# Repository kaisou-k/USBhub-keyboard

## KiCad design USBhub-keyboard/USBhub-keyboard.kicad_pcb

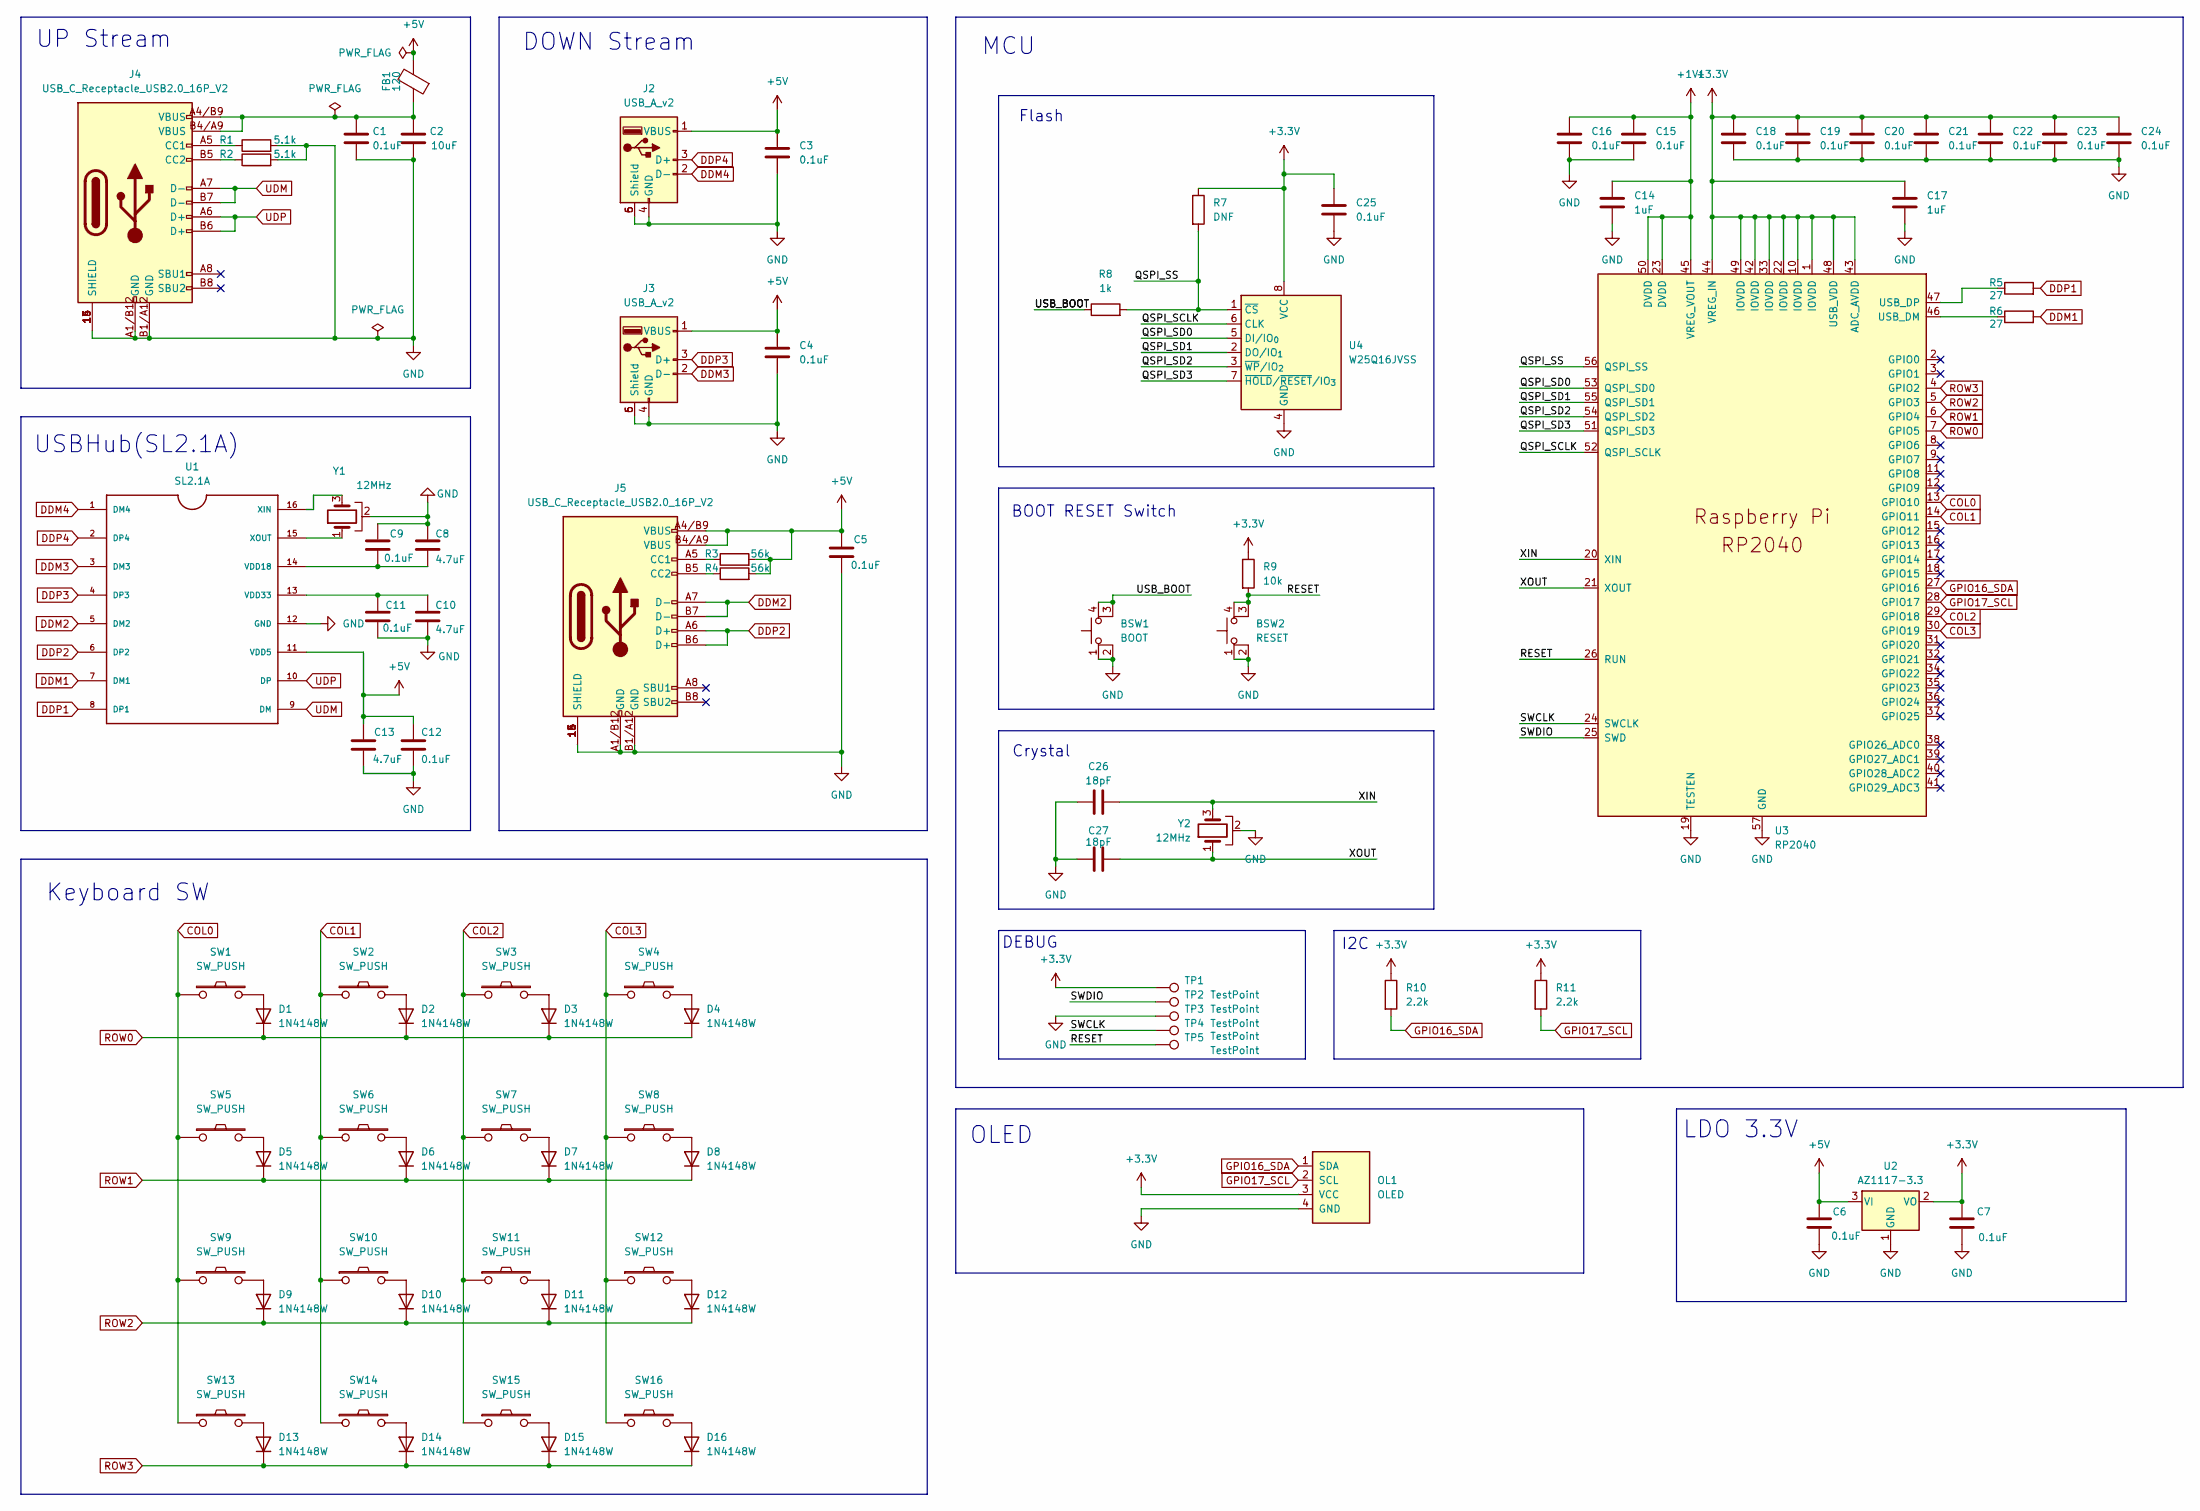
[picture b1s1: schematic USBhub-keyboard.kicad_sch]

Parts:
BSW1: BOOT; SW_TS04-66-50-BK-260-SMT
BSW2: RESET; SW_TS04-66-50-BK-260-SMT
C1, C3, C4, C5, C6, C7, C9, C11, C12, C15, C16, C18, C19, C20, C21, C22, C23, C24, C25: 0.1uF; C_0603_1608Metric
C2: 10uF; C_0805_2012Metric
C8, C10, C13: 4.7uF; C_1206_3216Metric
C14, C17: 1uF; C_0805_2012Metric
C26, C27: 18pF; C_0603_1608Metric
D1, D2, D3, D4, D5, D6, D7, D8, D9, D10, D11, D12, D13, D14, D15, D16: 1N4148W; D_SOD-123
FB1: 120; R_0603_1608Metric
J2, J3: USB_A_v2; 3210W1BCE
J4, J5: USB_C_Receptacle_USB2.0_16P_V2; CONN_8p94X6p5X3p16_12L_GCC
OL1: OLED; 128x64OLED
R1, R2: 5.1k; R_0603_1608Metric
R3, R4: 56k; R_0603_1608Metric
R5, R6: 27; R_0603_1608Metric
R7: DNF; R_0603_1608Metric
R8: 1k; R_0603_1608Metric
R9: 10k; R_0603_1608Metric
R10, R11: 2.2k; R_0603_1608Metric
SW1, SW2, SW3, SW4, SW5, SW6, SW7, SW8, SW9, SW10, SW11, SW12, SW13, SW14, SW15, SW16: SW_PUSH; CherryMX_Hotswap_via_1U
TP1, TP2, TP3, TP4, TP5: TestPoint; TestPoint_Pad_1.5x1.5mm
U1: SL2.1A; SO16
U2: AZ1117-3.3; SOT-223-3_TabPin2
U3: RP2040; RP2040-QFN-56
U4: W25Q16JVSS; SOIC-8_5.3x5.3mm_P1.27mm
Y1, Y2: 12MHz; Crystal_SMD_3225-4Pin_3.2x2.5mm

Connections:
+1V1: C14.1, C15.1, C16.1, U3.23 (DVDD), U3.45 (VREG_VOUT), U3.50 (DVDD)
+3.3V: C7.1, C17.1, C18.1, C19.1, C20.1, C21.1, C22.1, C23.1, C24.1, C25.1, OL1.3 (VCC), R7.1, R9.1, R10.1, R11.1, TP1.1, U2.2 (VO), U3.1 (IOVDD), U3.10 (IOVDD), U3.22 (IOVDD), U3.33 (IOVDD), U3.42 (IOVDD), U3.43 (ADC_AVDD), U3.44 (VREG_IN), U3.48 (USB_VDD), U3.49 (IOVDD), U4.8 (VCC); also elsewhere on the board
+5V: C3.1, C4.1, C5.1, C6.1, C12.1, C13.1, FB1.2, J2.1 (VBUS), J3.1 (VBUS), J5.A4/B9 (VBUS), J5.A9 (VBUS), J5.B4 (VBUS), J5.B4/A9 (VBUS), J5.B9 (VBUS), R3.2, R4.2, U1.11 (VDD5), U2.3 (VI)
/QSPI_SCLK: U3.52 (QSPI_SCLK), U4.6 (CLK)
/QSPI_SD0: U3.53 (QSPI_SD0), U4.5 (DI/IO_{0})
/QSPI_SD1: U3.55 (QSPI_SD1), U4.2 (DO/IO_{1})
/QSPI_SD2: U3.54 (QSPI_SD2), U4.3 (~WP/IO_{2})
/QSPI_SD3: U3.51 (QSPI_SD3), U4.7 (~HOLD/~RESET/IO_{3})
/QSPI_SS: R7.2, R8.2, U3.56 (QSPI_SS), U4.1 (~CS)
/RESET: BSW2.3 (K), BSW2.4 (A), R9.2, TP5.1, U3.26 (RUN); also elsewhere on the board
/SWCLK: TP4.1, U3.24 (SWCLK); also elsewhere on the board
/SWDIO: TP2.1, U3.25 (SWD); also elsewhere on the board
/USB_BOOT: BSW1.3 (K), BSW1.4 (A), R8.1
/XIN: C26.2, U3.20 (XIN), Y2.3
/XOUT: C27.2, U3.21 (XOUT), Y2.1
COL0: SW1.1, SW5.1, SW9.1, SW13.1, U3.13 (GPIO10)
COL1: SW2.1, SW6.1, SW10.1, SW14.1, U3.14 (GPIO11)
COL2: SW3.1, SW7.1, SW11.1, SW15.1, U3.29 (GPIO18)
COL3: SW4.1, SW8.1, SW12.1, SW16.1, U3.30 (GPIO19)
DDM1: R6.2, U1.7 (DM1)
DDM2: J5.A7 (D-), J5.B7 (D-), U1.5 (DM2)
DDM3: J3.2 (D-), U1.3 (DM3)
DDM4: J2.2 (D-), U1.1 (DM4)
DDP1: R5.2, U1.8 (DP1)
DDP2: J5.A6 (D+), J5.B6 (D+), U1.6 (DP2)
DDP3: J3.3 (D+), U1.4 (DP3)
DDP4: J2.3 (D+), U1.2 (DP4)
GND: BSW1.1, BSW1.2, BSW2.1, BSW2.2, C1.2, C2.2, C3.2, C4.2, C5.2, C6.2, C7.2, C8.1, C9.1, C10.2, C11.2, C12.2, C13.2, C14.2, C15.2, C16.2, C17.2, C18.2, C19.2, C20.2, C21.2, C22.2, C23.2, C24.2, C25.2, C26.1, C27.1, J2.4 (GND), J2.5 (Shield), J2.6 (Shield), J3.4 (GND), J3.5 (Shield), J3.6 (Shield), J4.13 (SHIELD), J4.14 (SHIELD), J4.15 (SHIELD), J4.16 (SHIELD), J4.A1/B12 (GND), J4.A12 (GND), J4.B1 (GND), J4.B1/A12 (GND), J4.B12 (GND), J5.13 (SHIELD), J5.14 (SHIELD), J5.15 (SHIELD), J5.16 (SHIELD), J5.A1/B12 (GND), J5.A12 (GND), J5.B1 (GND), J5.B1/A12 (GND), J5.B12 (GND), OL1.4 (GND), R1.2, R2.2, TP3.1, U1.12 (GND), U2.1 (GND), U3.19 (TESTEN), U3.57 (GND), U4.4 (GND), Y1.2, Y1.4, Y2.2, Y2.4; also elsewhere on the board
GPIO16_SDA: OL1.1 (SDA), R10.2, U3.27 (GPIO16)
GPIO17_SCL: OL1.2 (SCL), R11.2, U3.28 (GPIO17)
unnamed: C1.1, C2.1, FB1.1, J4.A4/B9 (VBUS), J4.A9 (VBUS), J4.B4 (VBUS), J4.B4/A9 (VBUS), J4.B9 (VBUS)
unnamed: D1.2 (A), SW1.2
unnamed: D2.2 (A), SW2.2
unnamed: D3.2 (A), SW3.2
unnamed: D4.2 (A), SW4.2
unnamed: D5.2 (A), SW5.2
unnamed: D6.2 (A), SW6.2
unnamed: D7.2 (A), SW7.2
unnamed: D8.2 (A), SW8.2
unnamed: D9.2 (A), SW9.2
unnamed: D10.2 (A), SW10.2
unnamed: D11.2 (A), SW11.2
unnamed: D12.2 (A), SW12.2
unnamed: D13.2 (A), SW13.2
unnamed: D14.2 (A), SW14.2
unnamed: D15.2 (A), SW15.2
unnamed: D16.2 (A), SW16.2
unnamed: J4.A5 (CC1), R1.1
unnamed: J4.B5 (CC2), R2.1
unnamed: J5.A5 (CC1), R3.1
unnamed: J5.B5 (CC2), R4.1
unnamed: C8.2, C9.2, U1.14 (VDD18)
unnamed: C10.1, C11.1, U1.13 (VDD33)
unnamed: U1.16 (XIN), Y1.3
unnamed: U1.15 (XOUT), Y1.1
unnamed: R6.1, U3.46 (USB_DM)
unnamed: R5.1, U3.47 (USB_DP)
ROW0: D1.1 (K), D2.1 (K), D3.1 (K), D4.1 (K), U3.7 (GPIO5)
ROW1: D5.1 (K), D6.1 (K), D7.1 (K), D8.1 (K), U3.6 (GPIO4)
ROW2: D9.1 (K), D10.1 (K), D11.1 (K), D12.1 (K), U3.5 (GPIO3)
ROW3: D13.1 (K), D14.1 (K), D15.1 (K), D16.1 (K), U3.4 (GPIO2)
UDM: J4.A7 (D-), J4.B7 (D-), U1.9 (DM)
UDP: J4.A6 (D+), J4.B6 (D+), U1.10 (DP)

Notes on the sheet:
UP Stream
I2C
Flash
BOOT RESET Switch
OLED
Crystal
DOWN Stream
Keyboard SW
MCU
USBHub(SL2.1A)
LDO 3.3V
DEBUG

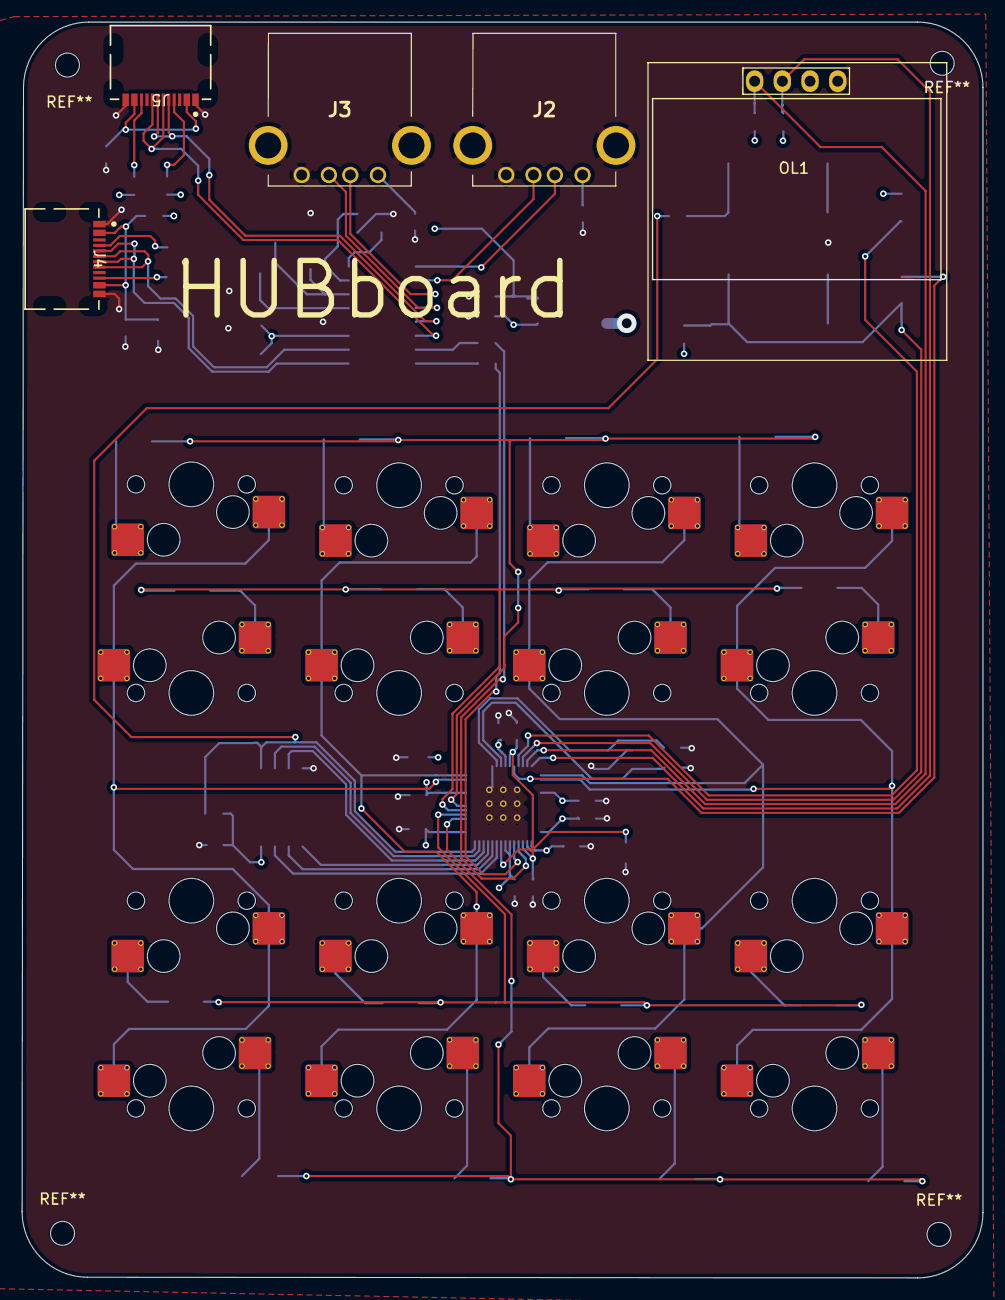
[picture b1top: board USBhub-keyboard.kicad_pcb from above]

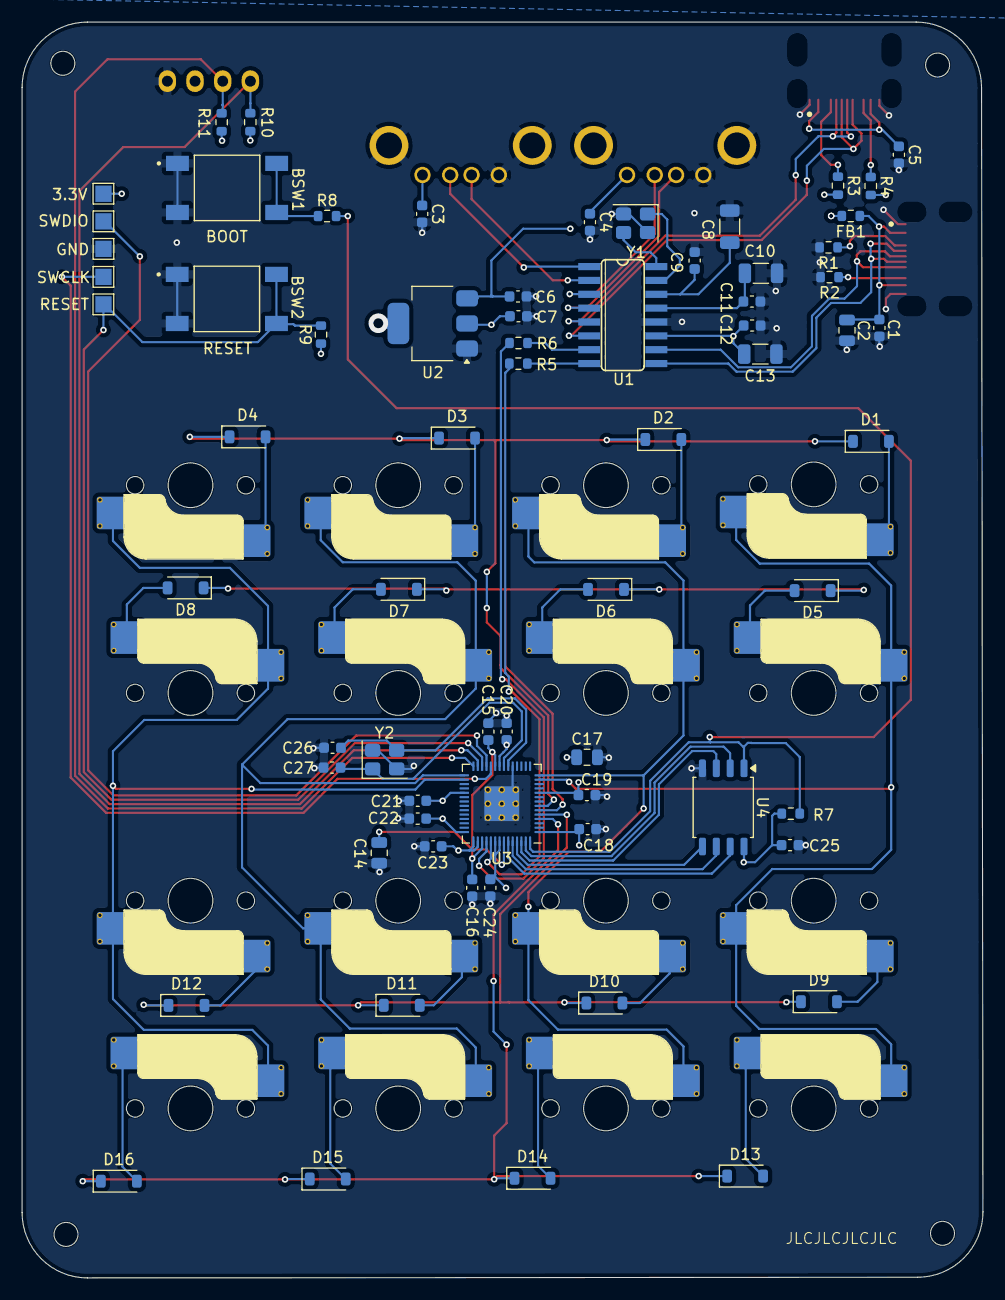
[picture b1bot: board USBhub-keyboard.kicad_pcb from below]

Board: 4 copper layers, 88.1 x 115.2 mm, 89 parts (68 on the bottom side), 63 nets.

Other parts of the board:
3.3V: TestPoint; TestPoint_Pad_1.5x1.5mm
GND: TestPoint; TestPoint_Pad_1.5x1.5mm
RESET: TestPoint; TestPoint_Pad_1.5x1.5mm
SWCLK: TestPoint; TestPoint_Pad_1.5x1.5mm
SWDIO: TestPoint; TestPoint_Pad_1.5x1.5mm

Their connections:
+3.3V: 3.3V.1 (1_1); also elsewhere on the board
/RESET: RESET.1 (1_1); also elsewhere on the board
/SWCLK: SWCLK.1 (1_1); also elsewhere on the board
/SWDIO: SWDIO.1 (1_1); also elsewhere on the board
GND: GND.1 (1_1); also elsewhere on the board

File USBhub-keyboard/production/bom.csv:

Designator,Footprint,Quantity,Value,LCSC Part #
"3.3V, GND, RESET, SWCLK, SWDIO",TestPoint_Pad_1.5x1.5mm,5,TestPoint,
BSW1,SW_TS04-66-50-BK-260-SMT,1,BOOT,
BSW2,SW_TS04-66-50-BK-260-SMT,1,RESET,
"C1, C11, C12, C15, C16, C18, C19, C20, C21, C22, C23, C24, C25, C3, C4, C5, C6, C7, C9",0603,19,0.1uF,
"C10, C13, C8",1206,3,4.7uF,
"C14, C17",0805,2,1uF,
C2,0805,1,10uF,
"C26, C27",0603,2,18pF,
"D1, D10, D11, D12, D13, D14, D15, D16, D2, D3, D4, D5, D6, D7, D8, D9",D_SOD-123,16,1N4148W,
FB1,0603,1,120,
"J2, J3",3210W1BCE,2,USB_A_v2,
"J4, J5",CONN_8p94X6p5X3p16_12L_GCC,2,USB_C_Receptacle_USB2.0_16P_V2,
OL1,128x64OLED,1,OLED,
"R1, R2",0603,2,5.1k,
"R10, R11",0603,2,2.2k,
"R3, R4",0603,2,56k,
"R5, R6",0603,2,27,
R7,0603,1,DNF,
R8,0603,1,1k,
R9,0603,1,10k,
"SW1, SW10, SW11, SW12, SW13, SW14, SW15, SW16, SW2, SW3, SW4, SW5, SW6, SW7, SW8, SW9",CherryMX_Hotswap_via_1U,16,SW_PUSH,
U1,SO16,1,SL2.1A,
U2,SOT-223-3_TabPin2,1,AZ1117-3.3,
U3,RP2040-QFN-56,1,RP2040,
U4,SOIC-8_5.3x5.3mm_P1.27mm,1,W25Q16JVSS,
"Y1, Y2",Crystal_SMD_3225-4Pin_3.2x2.5mm,2,12MHz,
